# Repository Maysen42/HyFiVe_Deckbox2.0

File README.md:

# HyFiVe - Hydrography on Fishing Vessels

<figure> 
   
</figure>

## Project Background 
Whether for modelling climate change or for our understanding of fish stocks – ocean data is essential for many disciplines. Usually, this data is collected by research vessels, which are cost-intensive and thus limited in space and time. To increase data resolution ‘vessels of opportunity’ can be a scalable alternative. In this concept vessels are used as measuring platforms, that are originally financed for a non-scientific purpose. Especially fishing vessels are of interest as they deploy gear in deep water and so make the whole water column accessible for an attached measuring system.

For this use case we developed a very flexible autonomous measuring system, which can be deployed on fishing gear to collect data in an affordable and scalable way. This was done within the **project ‘Hydrography on Fishing Vessels - HyFiVe’**
- Project period: Sept 2021 until Sept 2024
- Project partners:  
    - Thünen-Institute of Baltic Sea Fisheries (TIOF), Rostock, Germany, [https://www.thuenen.de/en/institutes/baltic-sea-fisheries/projects/fisheries-and-survey-technology/hyfive-hydrography-on-fishing-vessels](https://www.thuenen.de/en/institutes/baltic-sea-fisheries/projects/fisheries-and-survey-technology/hyfive-hydrography-on-fishing-vessels)
    - Leibnitz-Institute for Baltic Sea Research Warnemünde (IOW), Germany [https://www.io-warnemuende.de/project/278/hyfive.html](https://www.io-warnemuende.de/project/278/hyfive.html)
    - Hensel Elektronik GmbH, Rostock, Germany [https://hensel-elektronik.de](https://hensel-elektronik.de)
- Project webpage: hyfive.info
- Contact: See hyfive.info

## The HyFiVe System

This measuring system essentially consists of three components: 
- [01 Logger](./01_Logger/): Measures data with implemented OEM sensors while in the water and transmits them wireless afterwards.
- [02 Deck box](./02_Deckbox/): Receives measuring data via wifi, geo-references and stores it, visualizes it locally via webservice and transmits it to shore. The deck box also forwards config updates from server to loggers.
- [03 Land-Based Server](./03_Server/): Central infrastructure with a relational database, a configuration interface for remote maintenance and a tool for visualization of measuring data.

As overarching topic, [bi-directional communication](./bi_directional_communication/) between these components is described separately. 

The HyFiVe system offers many advantages:
- Autonomous operation up to several month
- Usable for non-experts, robust design
- Affordable price 
- Near live transmission of geo-referenced data to shore
- Scalability: Designed for a growing fleet of loggers and deck boxes
- Flexibility: Tested in various use cases, e.g. on trawl nets, as handheld probe and on sailing vessels 
- Modular design of logger facilitating easy change of sensors and integration of new ones
- Bi-directional data flow offering possibilities for remote servicing (VPN to deck box, config.json file for logger) 
- Comprehensive meta data
- Use of open sub-components and open standards lowering costs and facilitating reuse (e.g. ESP32, Raspberry Pi, nodeRed, InfluxDB, netcdf, https://cfconventions.org/ for naming variables)
- Open source, so you can modify and commercialise (according to the licenses below)

The system was developed in an agile method, so prototypes were built from an early stage on and tested continuously. Till the end of the first project in Sept 2024 the system was deployed on over ten vessels, among them research vessels, trawl fishing vessels, gill net fishing vessels and recreational vessels like sailing boats. 

<figure> 

   <figurecaption><a name="figure1">*Figure 1:*</a> *Logger, deck box and server - the three components of the HyFiVe measuring system*</figurecaption>
</figure>

## Github Repository
This documentation is aimed to enable you to build an own HyFiVe system and therefore contains detailed informations about all parts. If you are interested in building a system and lack information, please get in contact with us. 

**Disclaimer: We do not guarantee that the description is accurate throughout or complete. All your work is done at your own risk. Please comply with all necessary and legal safety precautions, especially when high voltage is involved, to avoid damage to yourself, others and the hardware.**

The three components have separate folders with hardware, software and specific information including READMEs which can be followed step by step. The READMEs contain
- Purpose and short description
- Used tools (hardware and software)
- Bills of Materials
- Additional information in the making/deploying

## Licenses
HyFiVe is an open-source project consisting of software, hardware, and documentation components. Each part of this project is licensed under a different copyleft license to ensure it remains free and open:

- Software/Code is licensed under [MPL-2.0](LICENSE_MPL-2.0)
- Hardware is licensed under [CERN-OHL-W-2.0 or later](LICENSE_CERN-OHL-W-2.0)
- Documentation is licensed under [CC-BY-SA-4.0](LICENSE_CC-BY-SA-4.0)

The HyFiVe logo is not published under above licenses and not free to use. 

An overview of the legal implications resulting from this licenses can be fund under [https://joinup.ec.europa.eu/collection/eupl/solution/joinup-licensing-assistant/jla-find-and-compare-software-licenses](https://joinup.ec.europa.eu/collection/eupl/solution/joinup-licensing-assistant/jla-find-and-compare-software-licenses).

## Funding
This project was funded by the German Federal Ministry of Food and Agriculture. 
<figure> 
   
</figure>

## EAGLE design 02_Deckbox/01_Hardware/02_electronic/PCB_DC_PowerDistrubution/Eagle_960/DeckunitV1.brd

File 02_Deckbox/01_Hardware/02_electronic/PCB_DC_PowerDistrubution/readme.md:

# Deck box - PCB for Power Distribution

Both power inputs of the deck box (DC and AC) are fed into this PCB (AC after converting to DC). The PCB holds a fuse and two diodes for backflow protection. So both power inputs can be connected at the same time without damage, and also both inputs are fed through the fuse.

More comprehensive documentation in [Hardware](../../)

<figure> 

   <figurecaption>*Functionality of PCB shown in diagram of power flow inside the deckbox*</figurecaption>
</figure>

---

<figure> 

   <figurecaption>*Picture of Board Design Rule file*</figurecaption>
</figure>

---

<figure> 

   <figurecaption>*Schematics of power distribution PCB*</figurecaption>
</figure>

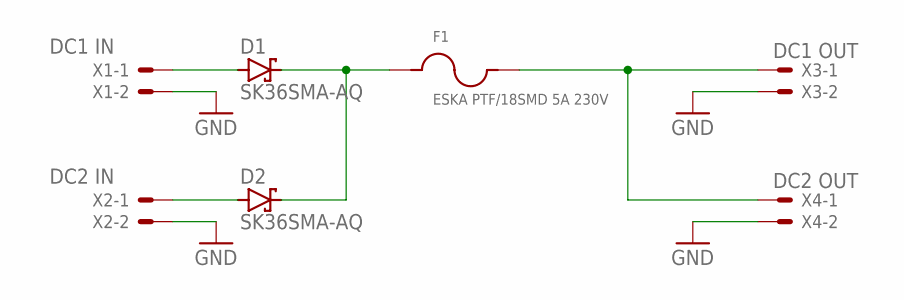
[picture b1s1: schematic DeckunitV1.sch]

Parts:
D1, D2: SK36SMA-AQ; SMA
F1: ESKA PTF/18SMD 5A 230V; 65800001109
X1: DC1 IN; 2PIN
X2: DC2 IN; 2PIN
X3: DC1 OUT; 2PIN
X4: DC2 OUT; 2PIN

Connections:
GND: X1.2, X2.2, X3.2, X4.2
V1+: D1.A, X1.1
V2+: D2.A, X2.1
V+: D1.C, D2.C, F1.1
V+F: F1.2, X3.1, X4.1

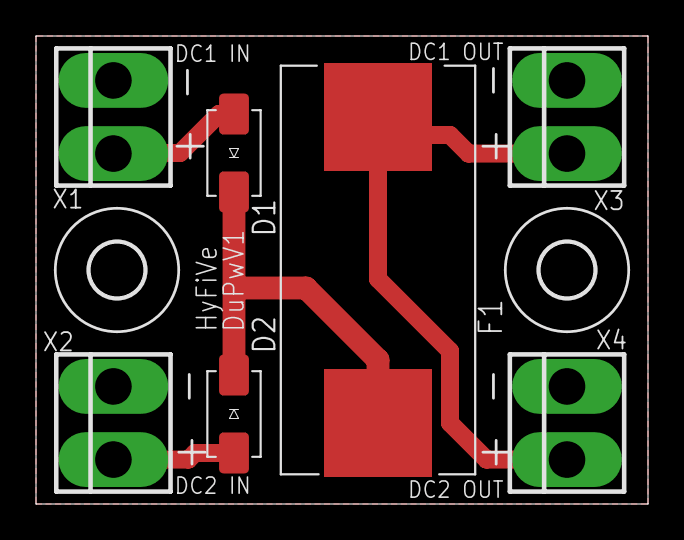
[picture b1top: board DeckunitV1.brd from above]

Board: 2 copper layers, 34.0 x 26.0 mm, 9 parts (0 on the bottom side), 5 nets.

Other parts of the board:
U$1, U$2: 3,0

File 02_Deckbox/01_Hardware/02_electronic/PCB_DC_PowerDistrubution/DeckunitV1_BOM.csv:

Part;Value;Device;Package;Description;DIGIKEY_PARTNO;MANUFACTURER;MPN;PACKAGE
D1;SK36SMA-AQ;SS12;SMA;DIODE SCHOTTKY 20V 1A SMA;SS12FSCT-ND;ON Semiconductor;SS12;SMA (DO-214AC)
D2;SK36SMA-AQ;SS12;SMA;DIODE SCHOTTKY 20V 1A SMA;SS12FSCT-ND;ON Semiconductor;SS12;SMA (DO-214AC)
F1;ESKA PTF/18SMD 5A 230V;65800001109;65800001109;FUSE BLOK CARTRIDGE 250V 10A SMD;WK6249TR-ND;Littelfuse Inc.;65800001109;65800001109
X1;DC1 IN;22-23-20212PIN;2PIN;Schraubklemmblock 1.5mm2 2-Pin RM3.5;1811290000-ND;Weidmueller;1811290000;2 PIN Through-Hole
X2;DC2 IN;22-23-20212PIN;2PIN;Schraubklemmblock 1.5mm2 2-Pin RM3.5;1811290000-ND;Weidmueller;1811290000;2 PIN Through-Hole
X3;DC1 OUT;22-23-20212PIN;2PIN;Schraubklemmblock 1.5mm2 2-Pin RM3.5;1811290000-ND;Weidmueller;1811290000;2 PIN Through-Hole
X4;DC2 OUT;22-23-20212PIN;2PIN;Schraubklemmblock 1.5mm2 2-Pin RM3.5;1811290000-ND;Weidmueller;1811290000;2 PIN Through-Hole

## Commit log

2024-08-08 initial commit
    Initial commit of the HyFiVe project
2024-08-09 added missing images
    Images for mechanics of deck box were missing
2024-09-06 Add modular logger files and change structure accordingly
2024-09-09 Initial Commit of Interfaceboard Software
2024-09-17 edited logger readmes and added pictures
2024-09-17 Rename logger_modular.JPG to logger_modular.jpg
2024-09-17 Rename electronic_mounting_modeled.PNG to electronic_mounting_modeled.png
2024-09-17 Minor fix for image positioning
2024-09-17 Update README.md
    trying to fix image positioning
2024-09-17 Test
2024-09-18 fixed some bugs
2024-09-18 Update main readme (introduction)
    and finally fixed issue with side-by-side positioning of figures in other readmes
2024-09-19 updated readmes (main plus logger)
2024-09-20 readmes updated (config update of logger, sensors and deckbox)
2024-09-23 updated readmes (deckbox; introducing bi-directional communication)
2024-09-24 updated readmes (server)
2024-09-24 updating readmes (minor fix)
2024-09-26 additional CAD-Files
    Adding F3D, STEP and PNG-Files for all relevant mechanical parts.
2024-09-30 update README.md to 02_Modular_Logger\01_Electronics
2024-10-01 update README.md to 02_Modular_Logger\03_Software
2024-10-10 firmware update 0.6
2024-10-11 Create nodered_all_flows_20241011.json
    Log content of the logger is also transmitted
2024-10-11 update Electronics for Modular_Logger
2024-10-11 folder structure adjusted
2024-10-14 Assembly Instructions 02_Modular_Logger
2024-10-14 fixed db query for vessels in deployments
2024-10-23 Update nodered_all_flows_20241011.json
    "Prepare data" and "Prepare Header" are connected to the store data
2024-11-07 firmware update V0.7
    Previously, if the battery was discharged below 5%, errors occurred during charging due to undervoltage
    This issue has been resolved with the current firmware update
2024-11-11 Charging process adjusted up to 100%, as battery-dependent variations are possible
    FW: 0.71
2024-11-11 fixed some path to python script bug
2024-11-20 added OTA (Over-The-Air) firmware update feature
    Firmware Update v0.80
    - Added OTA firmware update feature
    - Enhanced code comments
    - Optimized function behavior
    - Implemented Node-RED flow for OTA firmware updates (nodered_all_flows_20241120.json)
2024-12-10 The WiFi connection problems have been resolved. firmware update V0.81
2025-02-04 Update DeckunitV1_BOM.csv
    Some parts were replaced by better available equivalent parts from other manufacturers
2025-02-24 undervoltageProtection added
2025-07-07 Update README.md
    Update instruction for assembly of deckbox 2.0
2025-07-07 Update README.md
    corrections in formatting
2025-07-08 Update README.md
    minor additions
2025-07-08 added images
    added images for mounting antennas
2025-07-08 test changed images
2025-07-11 images for updated instructions
2025-07-11 Update README.md
    mounting antenna
2025-07-11 Update README.md
    finished top part
2025-07-11 Rename config_1_overview.PNG to config_1_overview.png
2025-07-15 Update README.md
    finished part about router
2025-07-15 add images to instructions
2025-07-15 added images of cage
2025-07-17 Update README.md
    Update BOM and Tools
2025-07-18 Update README.md
    new pictures fo weipu and gluing with sikaflex
2025-07-18 Update README.md
    fix format
2025-07-18 new picturs and updated holes drawing
2025-07-21 intructions for USB and Molex Plug
2025-07-21 some small fixes
2025-07-22 typos
2025-07-22 update layout
2025-07-22 add instructions for raspi case
2025-07-23 general alarm time update
2025-07-23 typos, new images for pcb connection
2025-07-23 new images for pcb connection
2025-07-23 correction on images
2025-07-25 Check and add missing GTINs
2025-07-25 typo
2025-07-25 CAD-Files updated
    Updated all CAD files to new Deckbox Version
2025-07-25 deleting old images
    Deleted old images
2025-07-25 add wiring diagram
2025-07-25 Deckbox Upgrade 2.0 to IP67 (#2)
    Update instruction for assembly of deckbox 2.0
    * Update README.md
    * added images for updated instructions
    * Update BOM and Tools
    * intructions for USB and Molex Plug
    Updated BOM.xlsx
